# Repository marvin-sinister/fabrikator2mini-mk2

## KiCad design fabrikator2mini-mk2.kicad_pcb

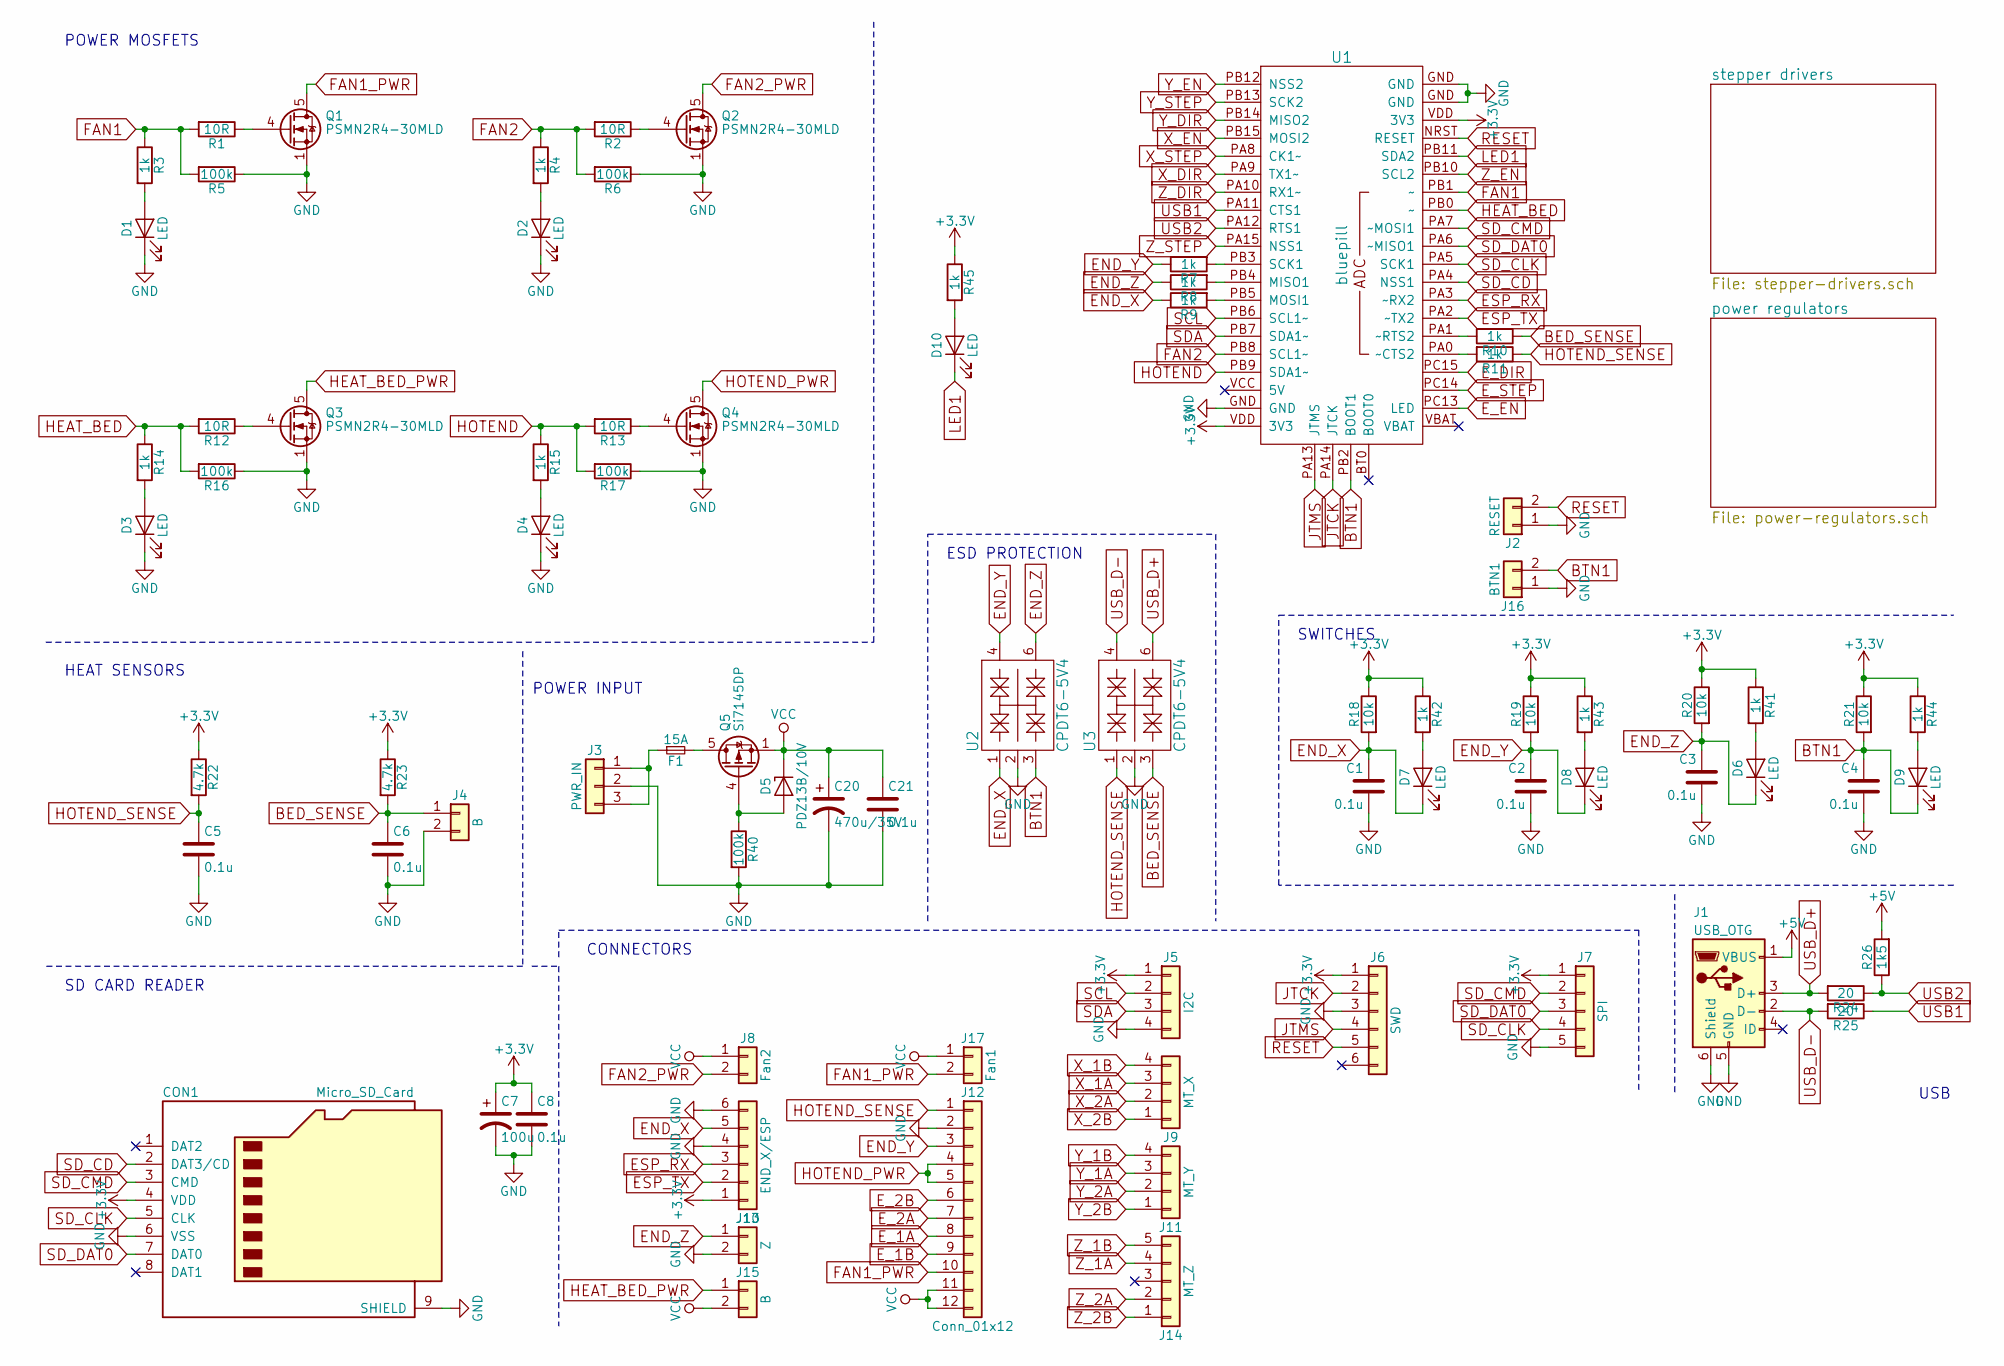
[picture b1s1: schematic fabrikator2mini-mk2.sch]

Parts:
C1, C2, C3, C4, C5, C6, C8, C21: 0.1u; C_0805_2012Metric_Pad1.15x1.40mm_HandSolder
C7: 100u; CP_Elec_8x10
C20: 470u/35V; CP_Radial_D10.0mm_P5.00mm
CON1: Micro_SD_Card; microSD_HC_Wuerth_693072010801
D1, D2, D3, D4, D6, D7, D8, D9, D10: LED; LED_0805_2012Metric_Pad1.15x1.40mm_HandSolder
D5: PDZ13B/10V; D_SOD-323_HandSoldering
F1: 15A; Fuseholder_Cylinder-5x20mm_Schurter_0031_8201_Horizontal_Op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
J1: USB_OTG; USB_Micro-B_Molex-105017-0001
J2: RESET; SW_SPST_B3S-1000
J3: PWR_IN; Hirose_DF63-3P-3.96DSA_1x03_P3.96mm_Horizontal
J4: B; JST_XH_B02B-XH-A_1x02_P2.50mm_Vertical
J5: I2C; JST_XH_B04B-XH-A_1x04_P2.50mm_Vertical
J6: SWD; Pin_Header_Straight_1x06_Pitch2.54mm
J7: SPI; JST_XH_B05B-XH-A_1x05_P2.50mm_Vertical
J8: Fan2; JST_PH_B2B-PH-K_1x02_P2.00mm_Vertical
J9: MT_X; JST_XH_B04B-XH-A_1x04_P2.50mm_Vertical
J10: END_X/ESP; JST_PH_B6B-PH-K_1x06_P2.00mm_Vertical
J11: MT_Y; JST_XH_B04B-XH-A_1x04_P2.50mm_Vertical
J12: Conn_01x12; JST_PH_B12B-PH-K_1x12_P2.00mm_Vertical
J13: Z; JST_XH_B02B-XH-A_1x02_P2.50mm_Vertical
J14: MT_Z; JST_XH_B05B-XH-A_1x05_P2.50mm_Vertical
J15: B; Hirose_DF63-2P-3.96DSA_1x02_P3.96mm_Horizontal
J16: BTN1; SW_Tactile_SPST_Angled_PTS645Vx58-2LFS
J17: Fan1; JST_PH_B2B-PH-K_1x02_P2.00mm_Vertical
Q1, Q2, Q3, Q4: PSMN2R4-30MLD; LFPAK33
Q5: Si7145DP; PowerPAK_SO-8_Single
R1, R2, R12, R13: 10R; R_0805_2012Metric_Pad1.15x1.40mm_HandSolder
R3, R4, R7, R8, R9, R10, R11, R14, R15, R41, R42, R43, R44, R45: 1k; R_0805_2012Metric_Pad1.15x1.40mm_HandSolder
R5, R6, R16, R17, R40: 100k; R_0805_2012Metric_Pad1.15x1.40mm_HandSolder
R18, R19, R20, R21: 10k; R_0805_2012Metric_Pad1.15x1.40mm_HandSolder
R22, R23: 4.7k; R_0805_2012Metric_Pad1.15x1.40mm_HandSolder
R24, R25: 20; R_0805_2012Metric_Pad1.15x1.40mm_HandSolder
R26: 1k5; R_0805_2012Metric_Pad1.15x1.40mm_HandSolder
U1: bluepill; blue_pill
U2, U3: CPDT6-5V4; SOT-23-6_Handsoldering

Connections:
+3V3: C7.1, C8.1, CON1.4 (VDD), J5.1, J6.1, J7.1, J10.1, R18.1, R19.1, R20.1, R21.1, R22.1, R23.1, R41.1, R42.1, R43.1, R44.1, R45.1, U1.VDD (3V3); also elsewhere on the board
+5V: J1.1 (VBUS), R26.2
BED_SENSE: C6.1, J4.1, R10.1, R23.2, U3.3
BTN1: C4.1, D9.1 (K), J16.2, R21.2, U1.PB2 (BOOT1), U2.3
END_X: C1.1, D7.1 (K), J10.5, R9.1, R18.2, U2.1
END_Y: C2.1, D8.1 (K), J12.3, R7.1, R19.2, U2.4
END_Z: C3.1, D6.1 (K), J13.1, R8.1, R20.2, U2.6
ESP_RX: J10.3, U1.PA3 (~~RX2)
ESP_TX: J10.2, U1.PA2 (~~TX2)
E_1A: J12.8; also elsewhere on the board
E_1B: J12.9; also elsewhere on the board
E_2A: J12.7; also elsewhere on the board
E_2B: J12.6; also elsewhere on the board
E_DIR: U1.PC15; also elsewhere on the board
E_EN: U1.PC13 (LED); also elsewhere on the board
E_STEP: U1.PC14; also elsewhere on the board
FAN1: R1.2, R3.1, R5.2, U1.PB1 (~~)
FAN1_PWR: J12.10, J17.2, Q1.5 (D)
FAN2: R2.2, R4.1, R6.2, U1.PB8 (SCL1~~)
FAN2_PWR: J8.2, Q2.5 (D)
GND: C1.2, C2.2, C3.2, C4.2, C5.2, C6.2, C7.2, C8.2, C20.2, C21.2, CON1.6 (VSS), CON1.9 (SHIELD), D1.1 (K), D2.1 (K), D3.1 (K), D4.1 (K), J1.5 (GND), J1.6 (Shield), J2.1, J3.2, J4.2, J5.4, J6.3, J7.5, J10.4, J10.6, J12.2, J13.2, J16.1, Q1.1 (S), Q1.2 (S), Q1.3 (S), Q2.1 (S), Q2.2 (S), Q2.3 (S), Q3.1 (S), Q3.2 (S), Q3.3 (S), Q4.1 (S), Q4.2 (S), Q4.3 (S), R5.1, R6.1, R16.1, R17.1, R40.2, U1.GND, U2.2, U2.5, U3.2, U3.5; also elsewhere on the board
HEAT_BED: R12.2, R14.1, R16.2, U1.PB0 (~~)
HEAT_BED_PWR: J15.1, Q3.5 (D)
HOTEND: R13.2, R15.1, R17.2, U1.PB9 (SDA1~~)
HOTEND_PWR: J12.4, J12.5, Q4.5 (D)
HOTEND_SENSE: C5.1, J12.1, R11.1, R22.2, U3.1
JTCK: J6.2, U1.PA14 (JTCK)
JTMS: J6.4, U1.PA13 (JTMS)
LED1: D10.1 (K), U1.PB11 (SDA2)
unnamed: D1.2 (A), R3.2
unnamed: D2.2 (A), R4.2
unnamed: D3.2 (A), R14.2
unnamed: D4.2 (A), R15.2
unnamed: D5.2 (A), Q5.4 (G), R40.1
unnamed: D6.2 (A), R41.2
unnamed: D7.2 (A), R42.2
unnamed: D8.2 (A), R43.2
unnamed: D9.2 (A), R44.2
unnamed: D10.2 (A), R45.2
unnamed: F1.1, J3.1, J3.3
unnamed: F1.2, Q5.5 (D)
unnamed: Q1.4 (G), R1.1
unnamed: Q2.4 (G), R2.1
unnamed: Q3.4 (G), R12.1
unnamed: Q4.4 (G), R13.1
unnamed: R7.2, U1.PB3 (SCK1)
unnamed: R8.2, U1.PB4 (MISO1)
unnamed: R9.2, U1.PB5 (MOSI1)
unnamed: R10.2, U1.PA1 (~~RTS2)
unnamed: R11.2, U1.PA0 (~~CTS2)
RESET: J2.2, J6.5, U1.NRST (RESET)
SCL: J5.2, U1.PB6 (SCL1~~)
SDA: J5.3, U1.PB7 (SDA1~~)
SD_CD: CON1.2 (DAT3/CD), U1.PA4 (NSS1)
SD_CLK: CON1.5 (CLK), J7.4, U1.PA5 (SCK1)
SD_CMD: CON1.3 (CMD), J7.2, U1.PA7 (~~MOSI1)
SD_DAT0: CON1.7 (DAT0), J7.3, U1.PA6 (~~MISO1)
USB1: R25.1, U1.PA11 (CTS1)
USB2: R24.1, R26.1, U1.PA12 (RTS1)
USB_D+: J1.3 (D+), R24.2, U3.6
USB_D-: J1.2 (D-), R25.2, U3.4
VCC: C20.1, C21.1, D5.1 (K), J8.1, J12.11, J12.12, J15.2, J17.1, Q5.1 (S), Q5.2 (S), Q5.3 (S); also elsewhere on the board
X_1A: J9.3; also elsewhere on the board
X_1B: J9.4; also elsewhere on the board
X_2A: J9.2; also elsewhere on the board
X_2B: J9.1; also elsewhere on the board
X_DIR: U1.PA9 (TX1~~); also elsewhere on the board
X_EN: U1.PB15 (MOSI2); also elsewhere on the board
X_STEP: U1.PA8 (CK1~~); also elsewhere on the board
Y_1A: J11.3; also elsewhere on the board
Y_1B: J11.4; also elsewhere on the board
Y_2A: J11.2; also elsewhere on the board
Y_2B: J11.1; also elsewhere on the board
Y_DIR: U1.PB14 (MISO2); also elsewhere on the board
Y_EN: U1.PB12 (NSS2); also elsewhere on the board
Y_STEP: U1.PB13 (SCK2); also elsewhere on the board
Z_1A: J14.4; also elsewhere on the board
Z_1B: J14.5; also elsewhere on the board
Z_2A: J14.2; also elsewhere on the board
Z_2B: J14.1; also elsewhere on the board
Z_DIR: U1.PA10 (RX1~~); also elsewhere on the board
Z_EN: U1.PB10 (SCL2); also elsewhere on the board
Z_STEP: U1.PA15 (NSS1); also elsewhere on the board

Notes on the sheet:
POWER MOSFETS
HEAT SENSORS
SD CARD READER
ESD PROTECTION
SWITCHES
CONNECTORS
USB
POWER INPUT

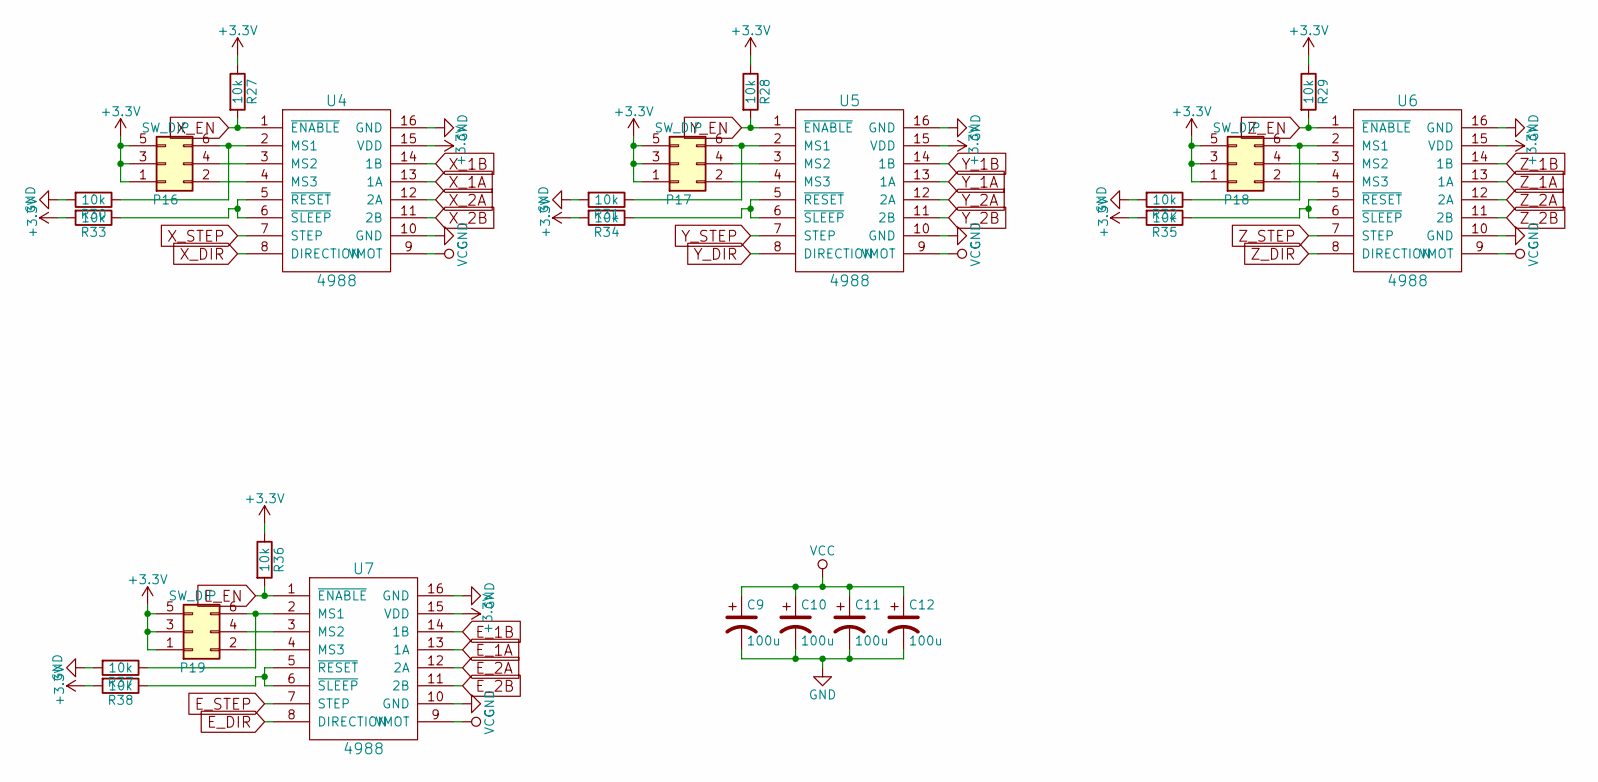
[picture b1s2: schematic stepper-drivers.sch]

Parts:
C9, C10, C11, C12: 100u; CP_Elec_8x10
P16, P17, P18, P19: SW_DIP; PinHeader_2x03_P2.54mm_Vertical
R27, R28, R29, R30, R31, R32, R33, R34, R35, R36, R37, R38: 10k; R_0805_2012Metric_Pad1.15x1.40mm_HandSolder
U4, U5, U6, U7: 4988; A4988

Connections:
+3V3: P16.1, P16.3, P16.5, P17.1, P17.3, P17.5, P18.1, P18.3, P18.5, P19.1, P19.3, P19.5, R27.1, R28.1, R29.1, R33.2, R34.2, R35.2, R36.1, R38.2, U4.15 (VDD), U5.15 (VDD), U6.15 (VDD), U7.15 (VDD); also elsewhere on the board
E_1A: U7.13 (1A); also elsewhere on the board
E_1B: U7.14 (1B); also elsewhere on the board
E_2A: U7.12 (2A); also elsewhere on the board
E_2B: U7.11 (2B); also elsewhere on the board
E_DIR: U7.8 (DIRECTION); also elsewhere on the board
E_EN: R36.2, U7.1 (~ENABLE); also elsewhere on the board
E_STEP: U7.7 (STEP); also elsewhere on the board
GND: C9.2, C10.2, C11.2, C12.2, R30.2, R31.2, R32.2, R37.2, U4.10 (GND), U4.16 (GND), U5.10 (GND), U5.16 (GND), U6.10 (GND), U6.16 (GND), U7.10 (GND), U7.16 (GND); also elsewhere on the board
unnamed: P16.2, U4.4 (MS3)
unnamed: P16.4, U4.3 (MS2)
unnamed: P16.6, R30.1, U4.2 (MS1)
unnamed: P17.2, U5.4 (MS3)
unnamed: P17.4, U5.3 (MS2)
unnamed: P17.6, R31.1, U5.2 (MS1)
unnamed: P18.2, U6.4 (MS3)
unnamed: P18.4, U6.3 (MS2)
unnamed: P18.6, R32.1, U6.2 (MS1)
unnamed: P19.2, U7.4 (MS3)
unnamed: P19.4, U7.3 (MS2)
unnamed: P19.6, R37.1, U7.2 (MS1)
unnamed: R33.1, U4.5 (~RESET), U4.6 (~SLEEP)
unnamed: R34.1, U5.5 (~RESET), U5.6 (~SLEEP)
unnamed: R35.1, U6.5 (~RESET), U6.6 (~SLEEP)
unnamed: R38.1, U7.5 (~RESET), U7.6 (~SLEEP)
VCC: C9.1, C10.1, C11.1, C12.1, U4.9 (VMOT), U5.9 (VMOT), U6.9 (VMOT), U7.9 (VMOT); also elsewhere on the board
X_1A: U4.13 (1A); also elsewhere on the board
X_1B: U4.14 (1B); also elsewhere on the board
X_2A: U4.12 (2A); also elsewhere on the board
X_2B: U4.11 (2B); also elsewhere on the board
X_DIR: U4.8 (DIRECTION); also elsewhere on the board
X_EN: R27.2, U4.1 (~ENABLE); also elsewhere on the board
X_STEP: U4.7 (STEP); also elsewhere on the board
Y_1A: U5.13 (1A); also elsewhere on the board
Y_1B: U5.14 (1B); also elsewhere on the board
Y_2A: U5.12 (2A); also elsewhere on the board
Y_2B: U5.11 (2B); also elsewhere on the board
Y_DIR: U5.8 (DIRECTION); also elsewhere on the board
Y_EN: R28.2, U5.1 (~ENABLE); also elsewhere on the board
Y_STEP: U5.7 (STEP); also elsewhere on the board
Z_1A: U6.13 (1A); also elsewhere on the board
Z_1B: U6.14 (1B); also elsewhere on the board
Z_2A: U6.12 (2A); also elsewhere on the board
Z_2B: U6.11 (2B); also elsewhere on the board
Z_DIR: U6.8 (DIRECTION); also elsewhere on the board
Z_EN: R29.2, U6.1 (~ENABLE); also elsewhere on the board
Z_STEP: U6.7 (STEP); also elsewhere on the board

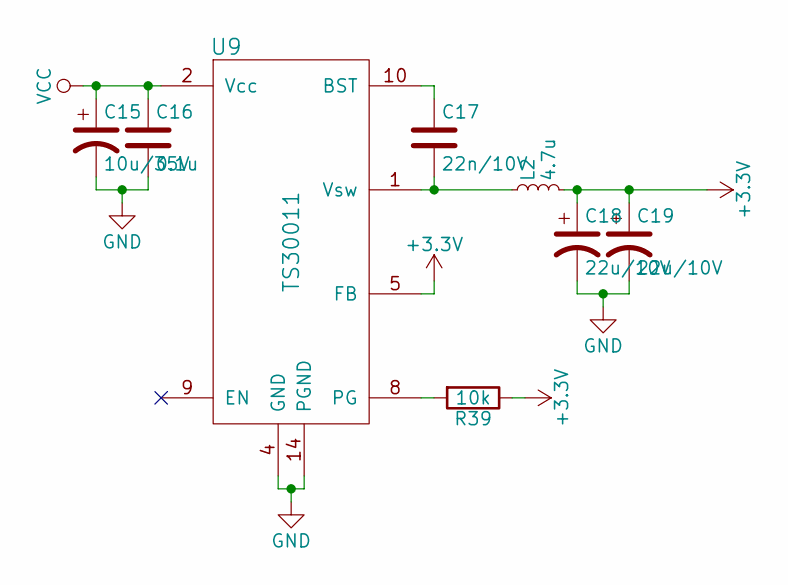
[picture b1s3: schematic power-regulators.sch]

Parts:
C15: 10u/35V; C_1206_3216Metric_Pad1.42x1.75mm_HandSolder
C16: 0.1u; C_0805_2012Metric_Pad1.15x1.40mm_HandSolder
C17: 22n/10V; C_0805_2012Metric_Pad1.15x1.40mm_HandSolder
C18, C19: 22u/10V; C_0805_2012Metric_Pad1.15x1.40mm_HandSolder
L2: 4.7u; L_Wuerth_WE-PD2-Typ-MS
R39: 10k; R_0805_2012Metric_Pad1.15x1.40mm_HandSolder
U9: TS30011; QFN-16-1EP_3x3mm_P0.5mm_EP1.8x1.8mm

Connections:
+3V3: C18.1, C19.1, L2.2, R39.1, U9.5 (FB); also elsewhere on the board
GND: C15.2, C16.2, C18.2, C19.2, U9.4 (GND), U9.14 (PGND), U9.15 (PGND), U9.17 (GND); also elsewhere on the board
unnamed: C17.1, U9.10 (BST)
unnamed: R39.2, U9.8 (PG)
VCC: C15.1, C16.1, U9.2 (Vcc), U9.3 (Vcc), U9.11 (Vcc); also elsewhere on the board
Vsw: C17.2, L2.1, U9.1 (Vsw), U9.12 (Vsw), U9.13 (Vsw), U9.16 (Vsw)

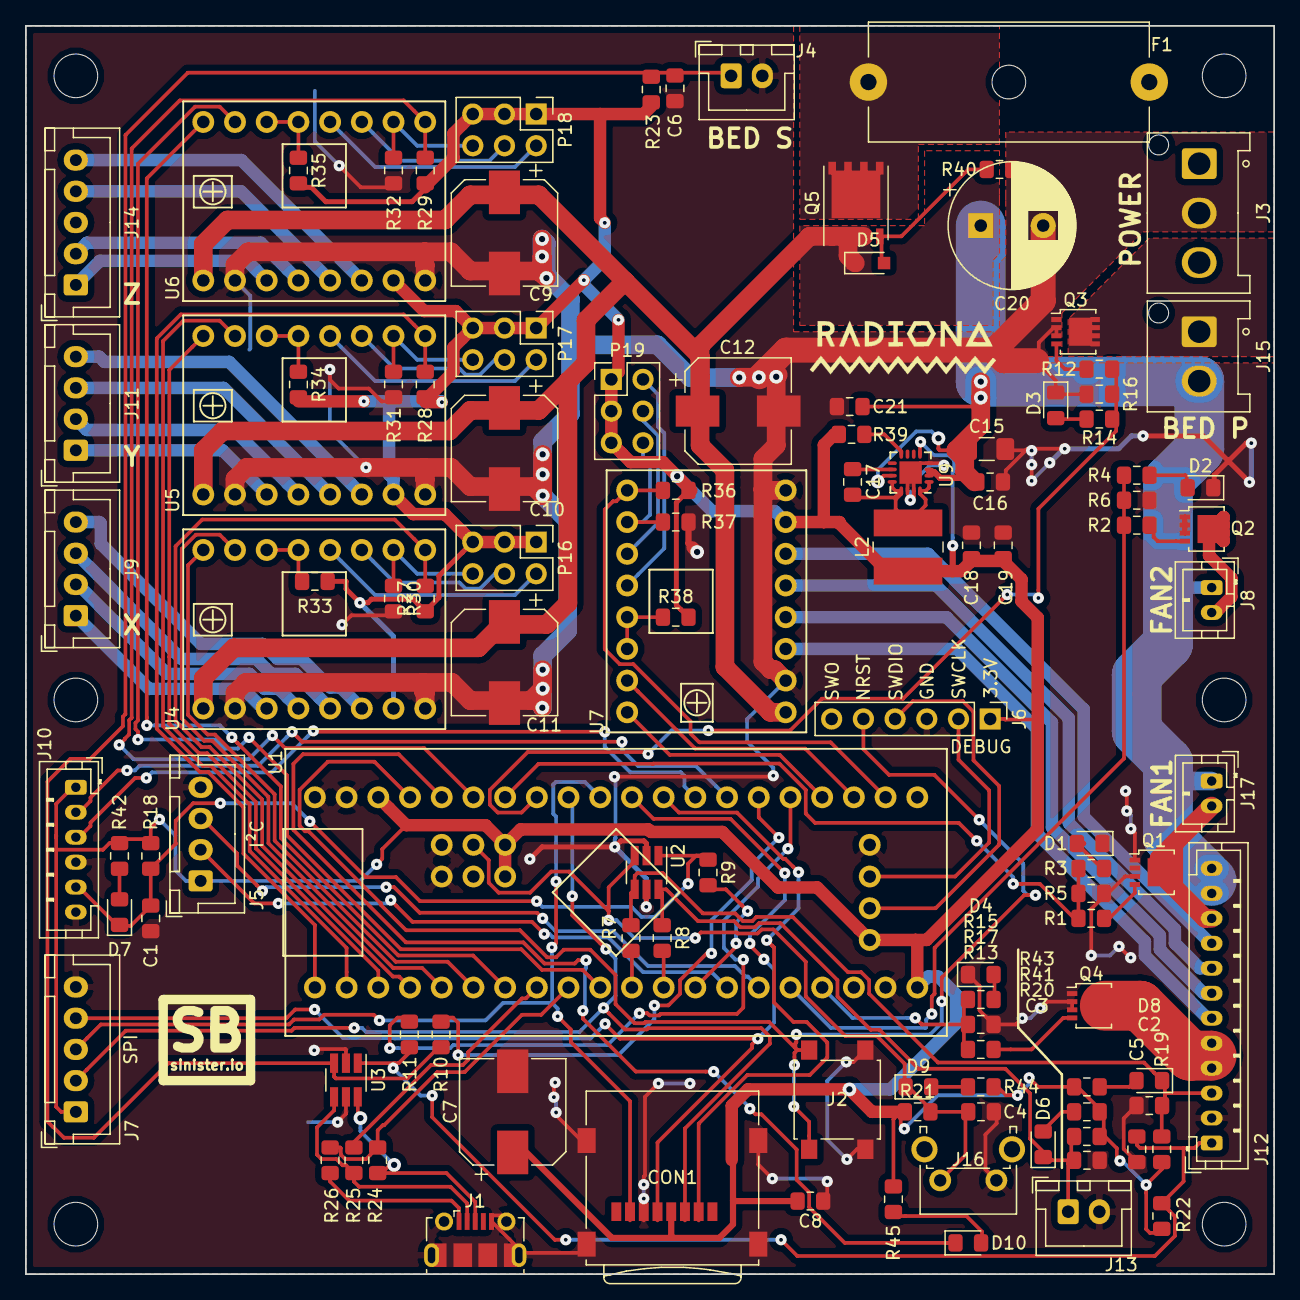
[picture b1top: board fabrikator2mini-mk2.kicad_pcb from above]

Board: 2 copper layers, 100.0 x 100.0 mm, 111 parts (0 on the bottom side), 102 nets.

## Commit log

2018-10-30 rerouted and removed 12V
2018-10-30 added
2018-10-30 rc1 route
2018-10-30 Power routing and stepper driver signals routed after MCU rotation
2018-10-30 Route most nets
2018-10-30 Fully routed
2018-10-31 added rescue-backup to ignore
2018-10-31 fixed untracked files
2018-10-31 silkscreen work
2018-10-31 updated with current schematics
2018-10-31 fixed symbols after switch to kicad 5
2018-10-31 fixed modules after switch to kicad 5
2018-10-31 rotated X Y Z connectos to correct orientation
2018-10-31 silkscreen corrections
